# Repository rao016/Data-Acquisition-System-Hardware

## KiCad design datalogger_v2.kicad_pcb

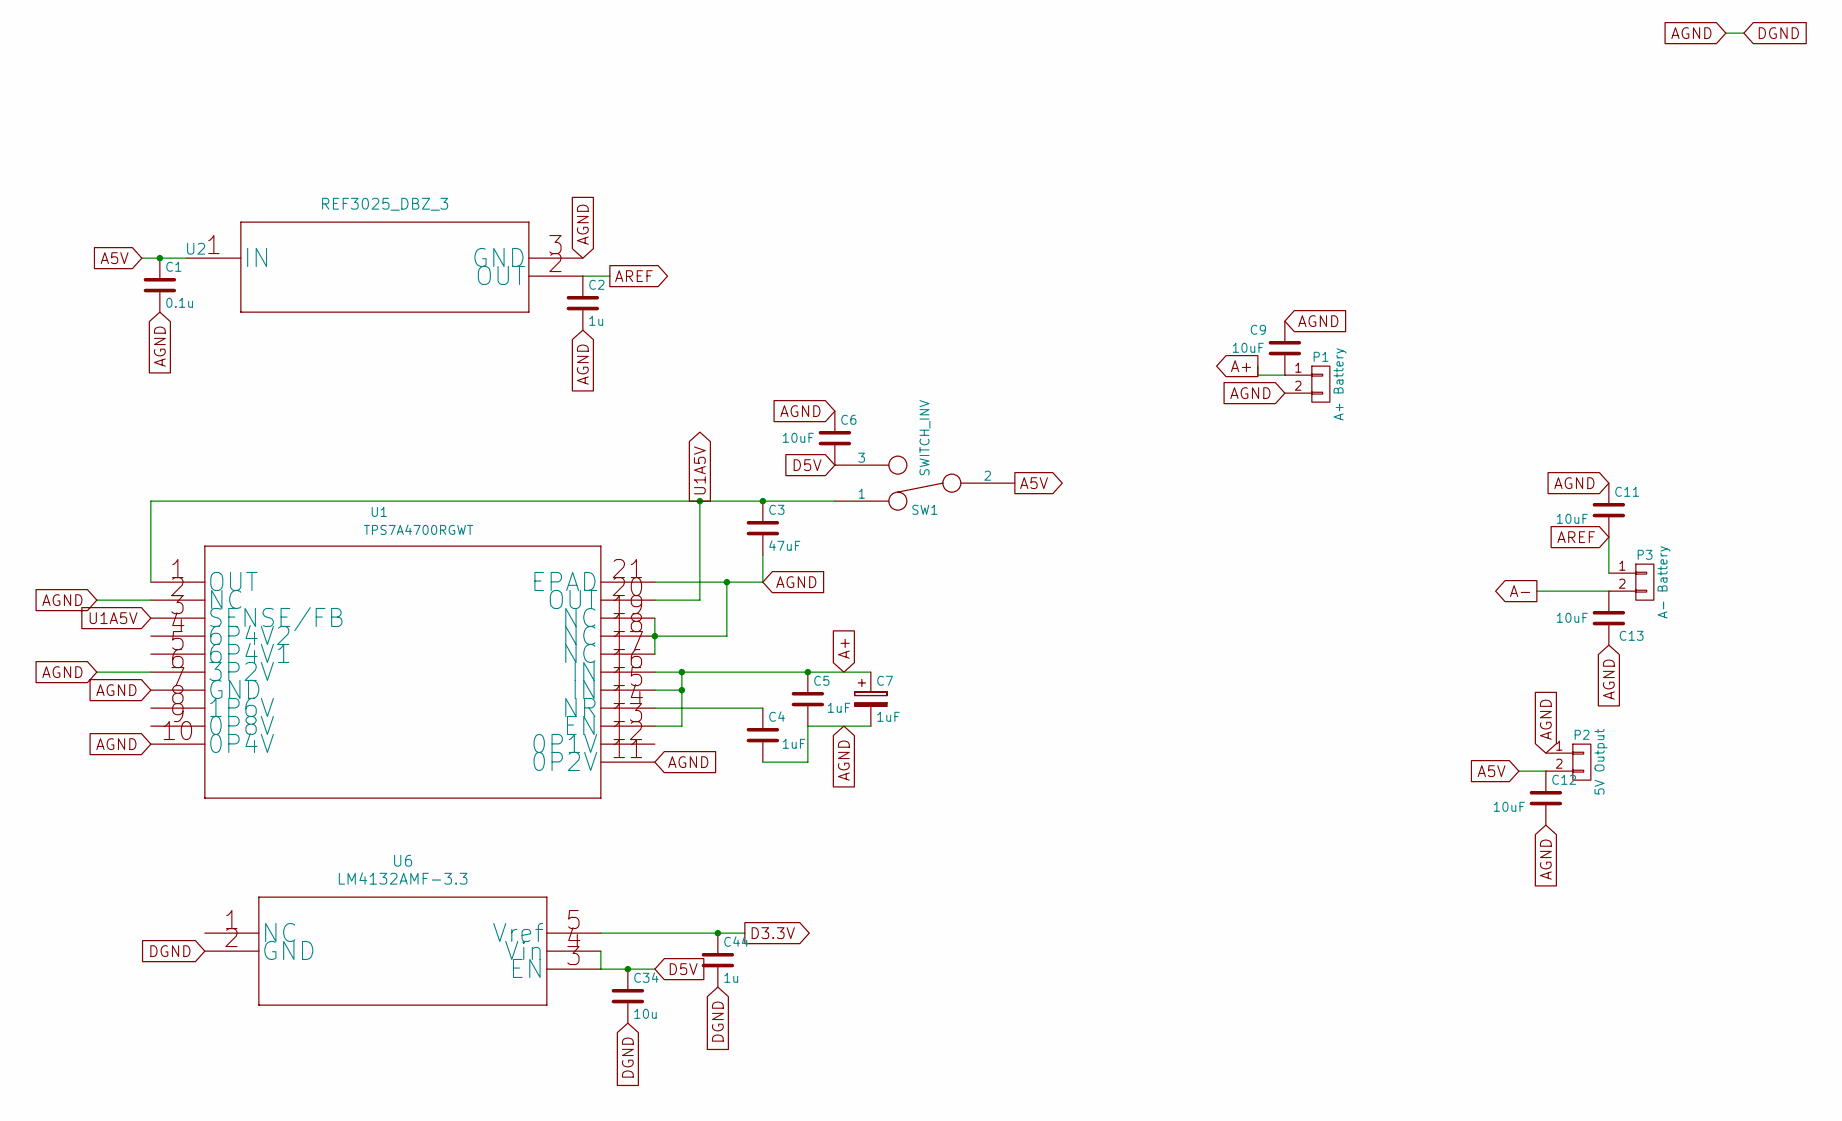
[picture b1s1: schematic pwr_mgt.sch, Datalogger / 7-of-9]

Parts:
C1: 0.1u; C_0402
C2, C44: 1u; C_0402
C3: 47uF; C_0805
C4, C5: 1uF; C_0402
C6, C9, C11, C12, C13: 10uF; C_0402
C7: 1uF; C_0603T
C34: 10u; C_0402
P1: A+ Battery; 2pinConn
P2: 5V Output; 2pinConn
P3: A- Battery; 2pinConn
SW1: SWITCH_INV; switch
U1: TPS7A4700RGWT; TPS7A470x
U2: REF3025_DBZ_3; REF3025AIDBZR
U6: LM4132AMF-3.3; LM4132AMF-1.8

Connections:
A5V: C1.1, C12.1, P2.2, SW1.2, U2.1 (IN); also elsewhere on the board
A+: C5.1, C7.1, C9.2, P1.1, U1.13 (EN), U1.15 (IN), U1.16 (IN)
A-: C13.1, P3.2
AGND: C1.2, C2.2, C3.2, C4.2, C5.2, C6.1, C7.2, C9.1, C11.1, C12.2, C13.2, C34.2, C44.2, P1.2, P2.1, U1.2 (NC), U1.6 (3P2V), U1.7 (GND), U1.10 (0P4V), U1.11 (0P2V), U1.17 (NC), U1.18 (NC), U1.19 (NC), U1.21 (EPAD), U2.3 (GND), U6.2 (GND); also elsewhere on the board
AREF: C2.1, C11.2, P3.1, U2.2 (OUT); also elsewhere on the board
D3.3V: C44.1, U6.5 (Vref); also elsewhere on the board
D5V: C6.2, C34.1, SW1.3, U6.3 (EN), U6.4 (Vin); also elsewhere on the board
unnamed: C4.1, U1.14 (NR)
U1A5V: C3.1, SW1.1, U1.1 (OUT), U1.3 (SENSE/FB), U1.20 (OUT)

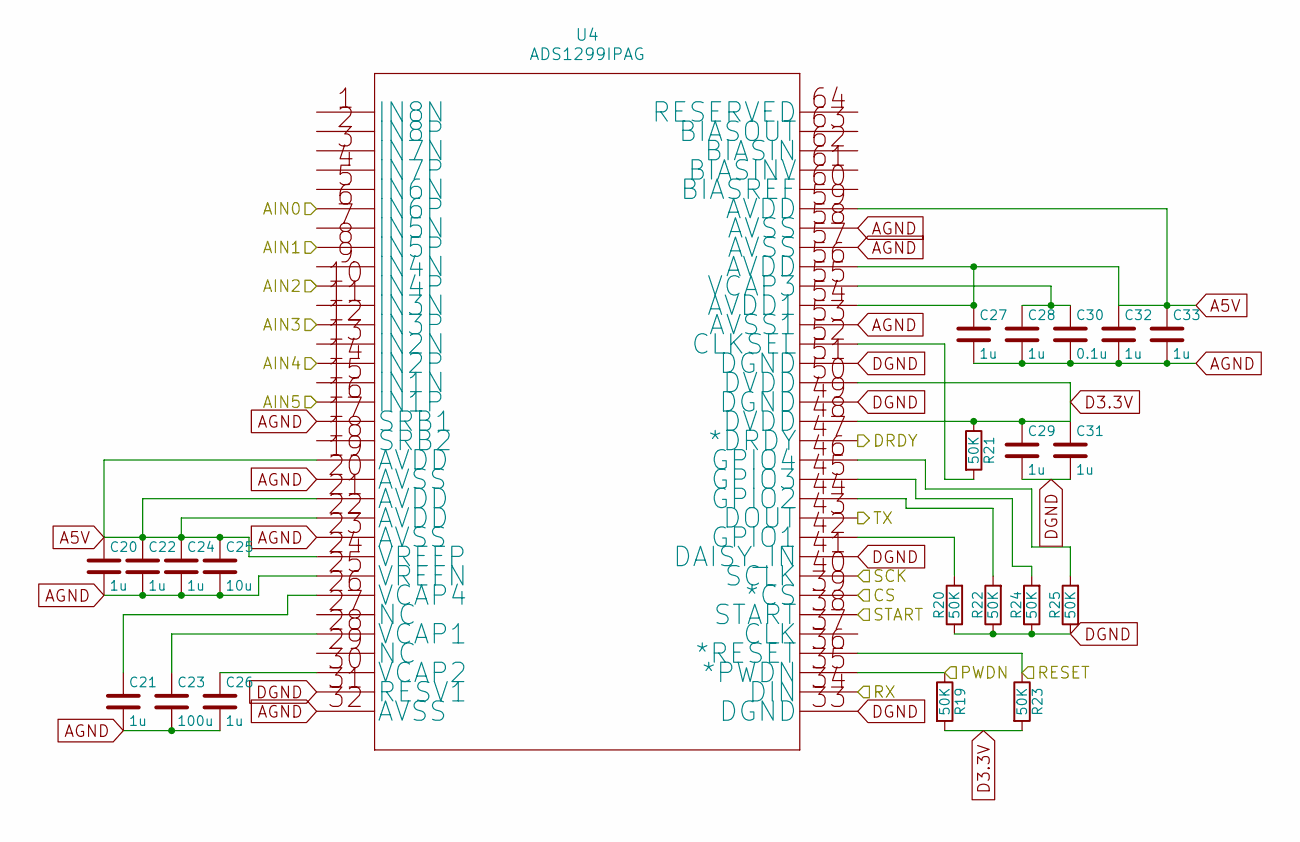
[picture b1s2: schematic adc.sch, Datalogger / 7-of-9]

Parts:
C20, C21, C22, C24, C26, C27, C28, C29, C31, C32, C33: 1u; C_0402
C23: 100u; C_1206
C25: 10u; C_0402
C30: 0.1u; C_0402
R19, R20, R21, R22, R23, R24, R25: 50K; R_0402
U4: ADS1299IPAG

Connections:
/ADC/AIN0: U4.6 (IN6P); also elsewhere on the board
/ADC/AIN1: U4.8 (IN5P); also elsewhere on the board
/ADC/AIN2: U4.10 (IN4P); also elsewhere on the board
/ADC/AIN3: U4.12 (IN3P); also elsewhere on the board
/ADC/AIN4: U4.14 (IN2P); also elsewhere on the board
/ADC/AIN5: U4.16 (IN1P); also elsewhere on the board
/ADC/CS: U4.39 (*CS); also elsewhere on the board
/ADC/DRDY: U4.47 (*DRDY); also elsewhere on the board
/ADC/PWDN: R19.1, U4.35 (*PWDN); also elsewhere on the board
/ADC/RESET: R23.1, U4.36 (*RESET); also elsewhere on the board
/ADC/RX: U4.34 (DIN); also elsewhere on the board
/ADC/SCK: U4.40 (SCLK); also elsewhere on the board
/ADC/START: U4.38 (START); also elsewhere on the board
/ADC/TX: U4.43 (DOUT); also elsewhere on the board
A5V: C20.1, C22.1, C24.1, C25.1, C27.1, C32.1, C33.1, U4.19 (AVDD), U4.21 (AVDD), U4.22 (AVDD), U4.24 (VREFP), U4.54 (AVDD1), U4.56 (AVDD), U4.59 (AVDD); also elsewhere on the board
AGND: C20.2, C21.2, C22.2, C23.2, C24.2, C25.2, C26.2, C27.2, C28.2, C29.2, C30.2, C31.2, C32.2, C33.2, R20.1, R22.1, R24.1, R25.1, U4.17 (SRB1), U4.20 (AVSS), U4.23 (AVSS), U4.25 (VREFN), U4.31 (RESV1), U4.32 (AVSS), U4.33 (DGND), U4.41 (DAISY_IN), U4.49 (DGND), U4.51 (DGND), U4.53 (AVSS1), U4.57 (AVSS), U4.58 (AVSS); also elsewhere on the board
D3.3V: C29.1, C31.1, R19.2, R21.1, R23.2, U4.48 (DVDD), U4.50 (DVDD); also elsewhere on the board
unnamed: C21.1, U4.26 (VCAP4)
unnamed: C23.1, U4.28 (VCAP1)
unnamed: C26.1, U4.30 (VCAP2)
unnamed: C28.1, C30.1, U4.55 (VCAP3)
unnamed 62: U4.15 (IN1N); also elsewhere on the board
unnamed 63: U4.13 (IN2N); also elsewhere on the board
unnamed 64: U4.11 (IN3N); also elsewhere on the board
unnamed 65: U4.9 (IN4N); also elsewhere on the board
unnamed 66: U4.7 (IN5N); also elsewhere on the board
unnamed 67: U4.5 (IN6N); also elsewhere on the board
unnamed: R20.2, U4.42 (GPIO1)
unnamed: R21.2, U4.52 (CLKSEL)
unnamed: R22.2, U4.44 (GPIO2)
unnamed: R24.2, U4.45 (GPIO3)
unnamed: R25.2, U4.46 (GPIO4)

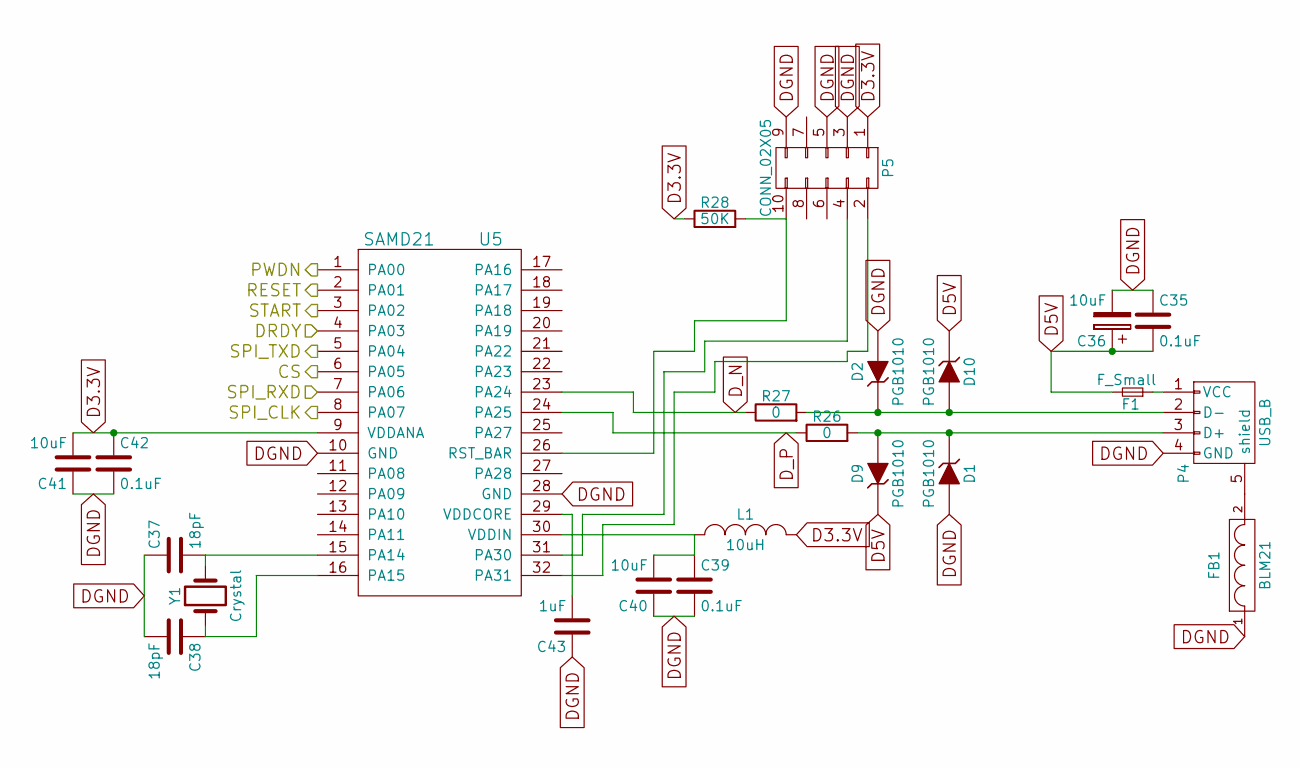
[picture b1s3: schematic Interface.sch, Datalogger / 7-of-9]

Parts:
C35, C39, C42: 0.1uF; C_0402
C36: 10uF; C_0603T
C37, C38: 18pF; C_0402
C40, C41: 10uF; C_0402
C43: 1uF; C_0402
D1, D2, D9, D10: PGB1010; D_0603
F1: F_Small; R_0603
FB1: BLM21; R_0805
L1: 10uH; C_0603
P4: USB_B; usbB
P5: CONN_02X05; Samtec-FTSH-105-01
R26, R27: 0; R_0402
R28: 50K; R_0402
U5: SAMD21; QFN-32-1EP_5x5mm_Pitch0.5mm
Y1: Crystal; crystal

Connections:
/Interface/CS: U5.6 (PA05); also elsewhere on the board
/Interface/DRDY: U5.4 (PA03); also elsewhere on the board
/Interface/PWDN: U5.1 (PA00); also elsewhere on the board
/Interface/RESET: U5.2 (PA01); also elsewhere on the board
/Interface/SPI_TXD: U5.5 (PA04); also elsewhere on the board
/Interface/START: U5.3 (PA02); also elsewhere on the board
/Level Shift/RX_MC: U5.7 (PA06); also elsewhere on the board
/Level Shift/SCK_MC: U5.8 (PA07); also elsewhere on the board
AGND: C35.1, C36.2, C37.1, C38.2, C39.2, C40.1, C41.1, C42.2, C43.1, D1.2 (A), D2.2 (A), FB1.1, P4.4 (GND), P5.3, P5.5, P5.9, U5.10 (GND), U5.28 (GND), U5.33, Y1.3, Y1.4; also elsewhere on the board
D3.3V: C41.2, C42.1, L1.2, P5.1, R28.1, U5.9 (VDDANA); also elsewhere on the board
D5V: C35.2, C36.1, D9.1 (K), D10.1 (K), F1.2; also elsewhere on the board
D_N: R27.1, U5.23 (PA24)
D_P: R26.1, U5.24 (PA25)
unnamed: C37.2, U5.15 (PA14), Y1.2
unnamed: C38.1, U5.16 (PA15), Y1.1
unnamed: C39.1, C40.2, L1.1, U5.30 (VDDIN)
unnamed: C43.2, U5.29 (VDDCORE)
unnamed: D1.1 (K), D9.2 (A), P4.3 (D+), R26.2
unnamed: D2.1 (K), D10.2 (A), P4.2 (D-), R27.2
unnamed: F1.1, P4.1 (VCC)
unnamed: FB1.2, P4.5 (shield)
unnamed: P5.2, U5.32 (PA31)
unnamed: P5.4, U5.31 (PA30)
unnamed: P5.10, R28.2, U5.26 (RST_BAR)

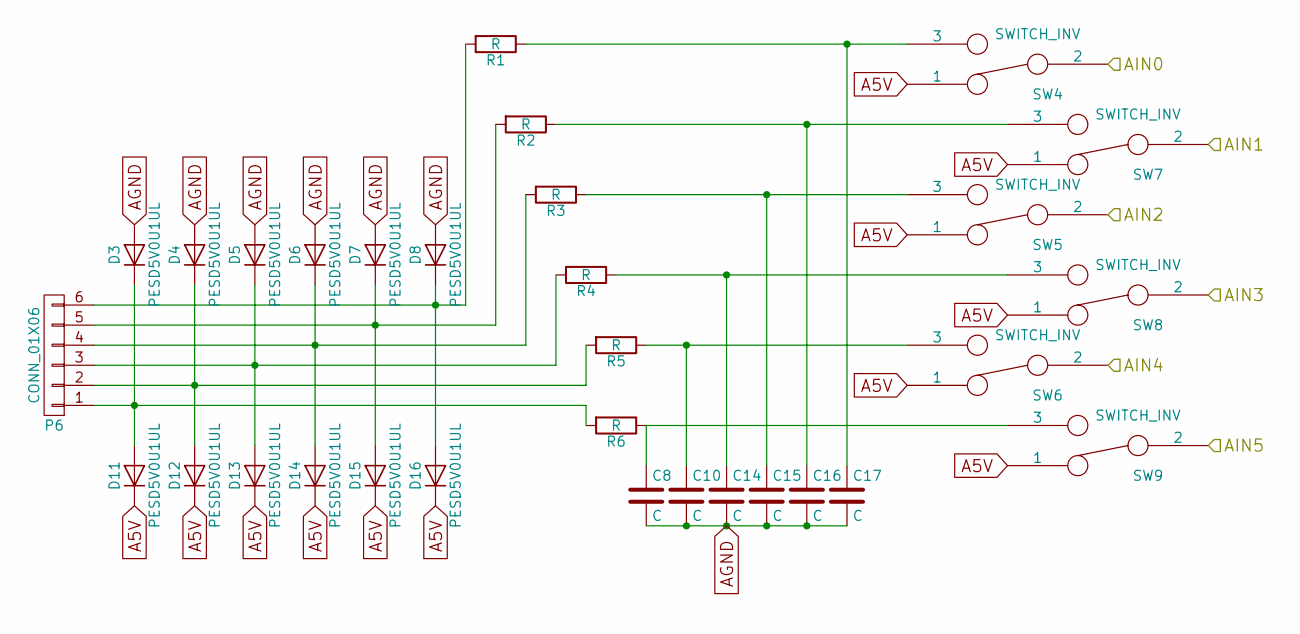
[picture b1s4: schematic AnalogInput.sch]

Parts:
C8, C10, C14, C15, C16, C17: C; C_0402
D3, D4, D5, D6, D7, D8, D11, D12, D13, D14, D15, D16: PESD5V0U1UL; SOD-523
P6: CONN_01X06; 6pinConn
R1, R2, R3, R4, R5, R6: R; R_0402
SW4, SW5, SW6, SW7, SW8, SW9: SWITCH_INV; switch

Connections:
/ADC/AIN0: SW4.2; also elsewhere on the board
/ADC/AIN1: SW7.2; also elsewhere on the board
/ADC/AIN2: SW5.2; also elsewhere on the board
/ADC/AIN3: SW8.2; also elsewhere on the board
/ADC/AIN4: SW6.2; also elsewhere on the board
/ADC/AIN5: SW9.2; also elsewhere on the board
A5V: D11.1 (K), D12.1 (K), D13.1 (K), D14.1 (K), D15.1 (K), D16.1 (K), SW4.1, SW5.1, SW6.1, SW7.1, SW8.1, SW9.1; also elsewhere on the board
AGND: C8.2, C10.2, C14.2, C15.2, C16.2, C17.2, D3.2 (A), D4.2 (A), D5.2 (A), D6.2 (A), D7.2 (A), D8.2 (A); also elsewhere on the board
unnamed: C8.1, R6.1, SW9.3
unnamed: C10.1, R5.1, SW6.3
unnamed: C14.1, R4.1, SW8.3
unnamed: C15.1, R3.1, SW5.3
unnamed: C16.1, R2.1, SW7.3
unnamed: C17.1, R1.1, SW4.3
unnamed: D3.1 (K), D11.2 (A), P6.1, R6.2
unnamed: D4.1 (K), D12.2 (A), P6.2, R5.2
unnamed: D5.1 (K), D13.2 (A), P6.3, R4.2
unnamed: D6.1 (K), D14.2 (A), P6.4, R3.2
unnamed: D7.1 (K), D15.2 (A), P6.5, R2.2
unnamed: D8.1 (K), D16.2 (A), P6.6, R1.2

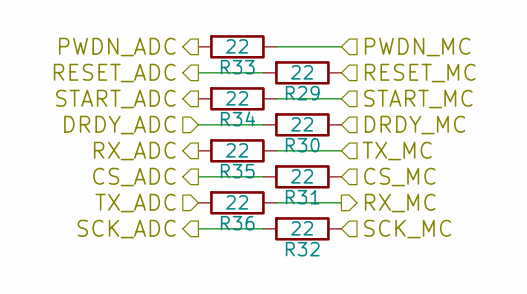
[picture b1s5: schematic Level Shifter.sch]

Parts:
R29, R30, R31, R32, R33, R34, R35, R36: 22; R_0402

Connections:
/ADC/CS: R31.2; also elsewhere on the board
/ADC/DRDY: R30.2; also elsewhere on the board
/ADC/PWDN: R33.2; also elsewhere on the board
/ADC/RESET: R29.2; also elsewhere on the board
/ADC/RX: R35.2; also elsewhere on the board
/ADC/SCK: R32.2; also elsewhere on the board
/ADC/START: R34.2; also elsewhere on the board
/ADC/TX: R36.2; also elsewhere on the board
/Interface/CS: R31.1; also elsewhere on the board
/Interface/DRDY: R30.1; also elsewhere on the board
/Interface/PWDN: R33.1; also elsewhere on the board
/Interface/RESET: R29.1; also elsewhere on the board
/Interface/SPI_TXD: R35.1; also elsewhere on the board
/Interface/START: R34.1; also elsewhere on the board
/Level Shift/RX_MC: R36.1; also elsewhere on the board
/Level Shift/SCK_MC: R32.1; also elsewhere on the board

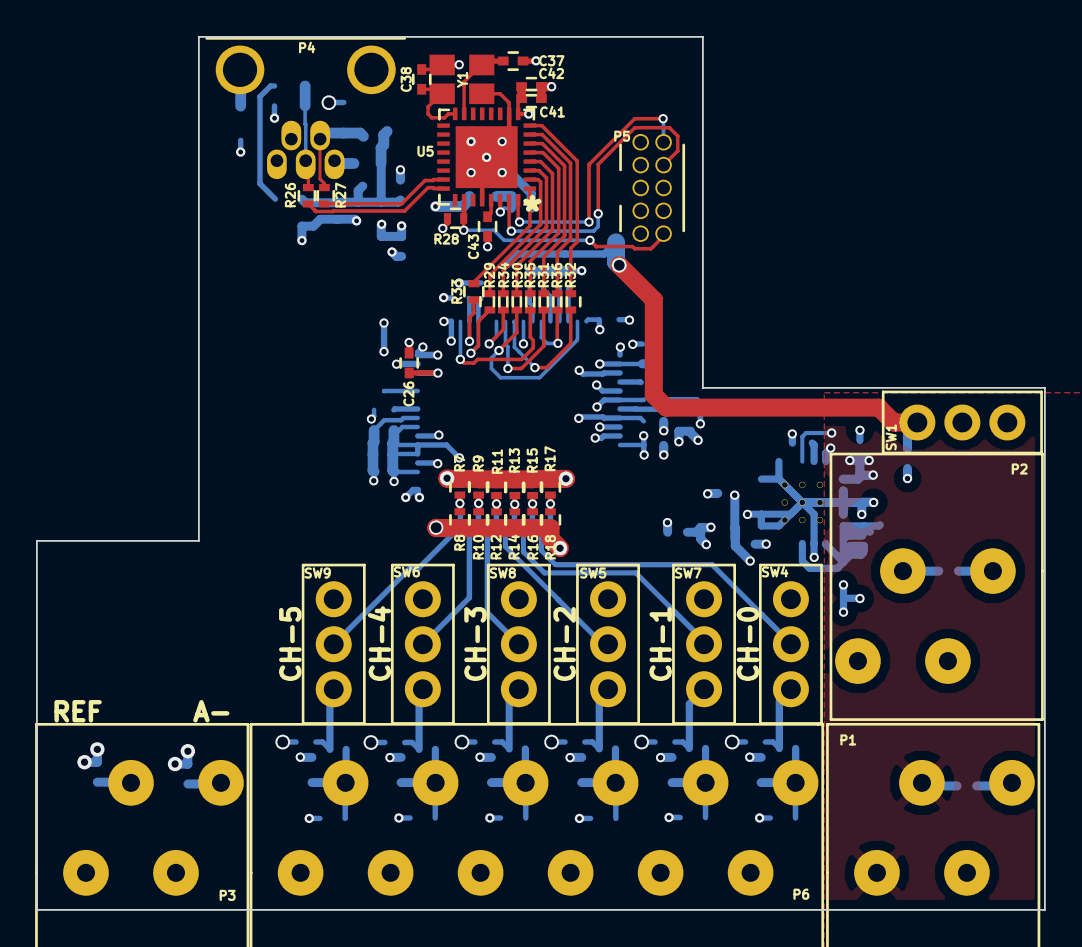
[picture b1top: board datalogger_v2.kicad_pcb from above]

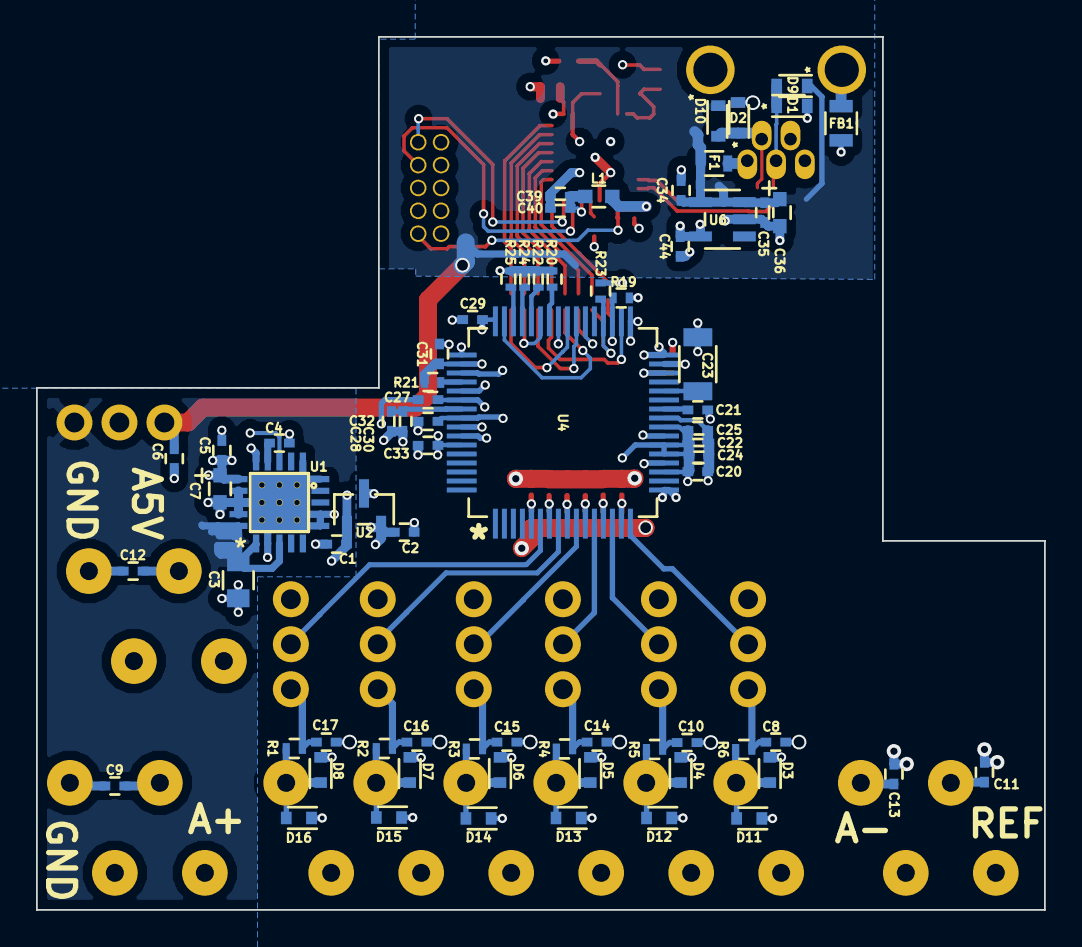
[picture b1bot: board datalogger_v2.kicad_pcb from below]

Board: 4 copper layers, 56.0 x 48.5 mm, 116 parts (72 on the bottom side), 71 nets.

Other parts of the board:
R7, R8, R9, R10, R11, R12, R13, R14, R15, R16, R17, R18: 0; R_0402

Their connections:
AGND: R7.2, R9.2, R11.2, R13.2, R15.2, R17.2; also elsewhere on the board
AREF: R8.2, R10.2, R12.2, R14.2, R16.2, R18.2; also elsewhere on the board
unnamed 62: R7.1, R8.1; also elsewhere on the board
unnamed 63: R9.1, R10.1; also elsewhere on the board
unnamed 64: R11.1, R12.1; also elsewhere on the board
unnamed 65: R13.1, R14.1; also elsewhere on the board
unnamed 66: R15.1, R16.1; also elsewhere on the board
unnamed 67: R17.1, R18.1; also elsewhere on the board

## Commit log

2018-02-05 Data Acquisition System Hardware
    Kicad Schematic and PCB

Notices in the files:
parts and their libraries:
Copyright 2016 Accelerated Designs. All rights reserved.
